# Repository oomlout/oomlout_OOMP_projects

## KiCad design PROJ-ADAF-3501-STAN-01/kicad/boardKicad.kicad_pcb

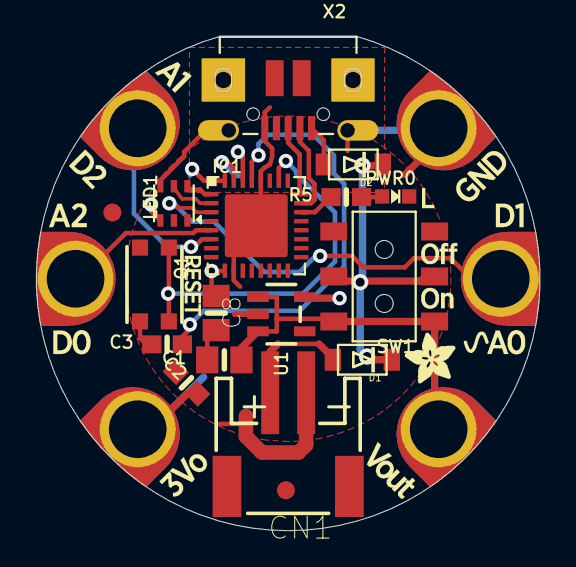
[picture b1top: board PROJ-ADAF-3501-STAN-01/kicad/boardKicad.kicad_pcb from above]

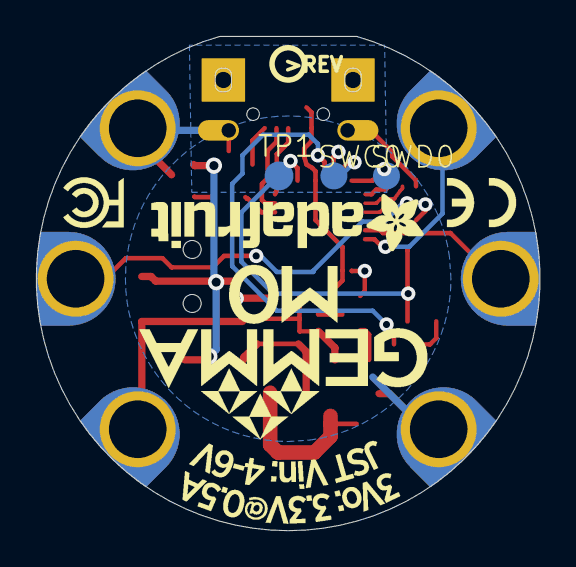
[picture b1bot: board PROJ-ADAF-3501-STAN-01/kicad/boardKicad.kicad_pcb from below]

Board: 16 copper layers, 28.0 x 27.5 mm, 29 parts (5 on the bottom side), 19 nets.

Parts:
B0, B1, B2: SEWTAP-ALLIGATOR; SEWALLI
C1, C8: 10uF; 0805-NO
C2, C3: 1uF; 0603-NO
CN1: JST-PH; JSTPH2
D1, D2: SCHOTTKY; SOD-123FL
GND0: SEWTAP-ALLIGATOR; SEWALLI
IC1: ATSAMD21E; QFN32_5MM
LED1: AP102-2020; APA102_2020
PWR0: red; CHIPLED_0603_NOOUTLINE
Q1: reset; BTN_KMR2_4.6X2.8
R5: 1K; 0603-NO
SW1: EG1218; EG1390
SWC0: TPTP15R; TP15R
SWD0: TPTP15R; TP15R
TP1: TPTP16R; TP16R
U1: AP2112K-3.3; SOT23-5
U$1, U$6: FIDUCIAL_1MM
U$7: GEMMA_M0_BOTTOM
U$8: GEMMA_M0_TOP
U$10: PCBFEAT-REV-040
UNK3V3: SEWTAP-ALLIGATOR; SEWALLI
VBAT0: SEWTAP-ALLIGATOR; SEWALLI
X2: MicroUSB; 4UCONN_20329_V2

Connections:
3.3V: C2.1, C8.1, IC1.9, IC1.30, LED1.3, U1.5, UNK3V3.P$1
D0_SDA_TX: B0.P$1, IC1.5
D1_A0: B1.P$1, IC1.3
D2_SCL_RX: B2.P$1, IC1.6
D3: IC1.1, LED1.6
D4: IC1.2, LED1.5
D13: IC1.22, R5.2
D+: IC1.24, X2.D+
D-: IC1.23, X2.D-
GND: C1.2, C2.2, C3.2, C8.2, CN1.1, GND0.P$1, IC1.10, IC1.28, IC1.33, LED1.4, PWR0.C, Q1.B, Q1.B', U1.2, X2.BASE@1, X2.BASE@2, X2.GND, X2.SPRT@1, X2.SPRT@2, X2.SPRT@3, X2.SPRT@4
unnamed: PWR0.A, R5.1
SWCLK: IC1.31, SWC0.TP
SWDIO: IC1.32, SWD0.TP
VBAT: CN1.2, D1.A
VBUS: D2.A, X2.VBUS
VDDCORE: C3.1, IC1.29
VHIGH: D1.C, D2.C, SW1.P1, SW1.P2
VOUT: C1.1, SW1.O1, SW1.O2, U1.1, U1.3, VBAT0.P$1
~RESET: IC1.26, Q1.A, Q1.A', TP1.TP

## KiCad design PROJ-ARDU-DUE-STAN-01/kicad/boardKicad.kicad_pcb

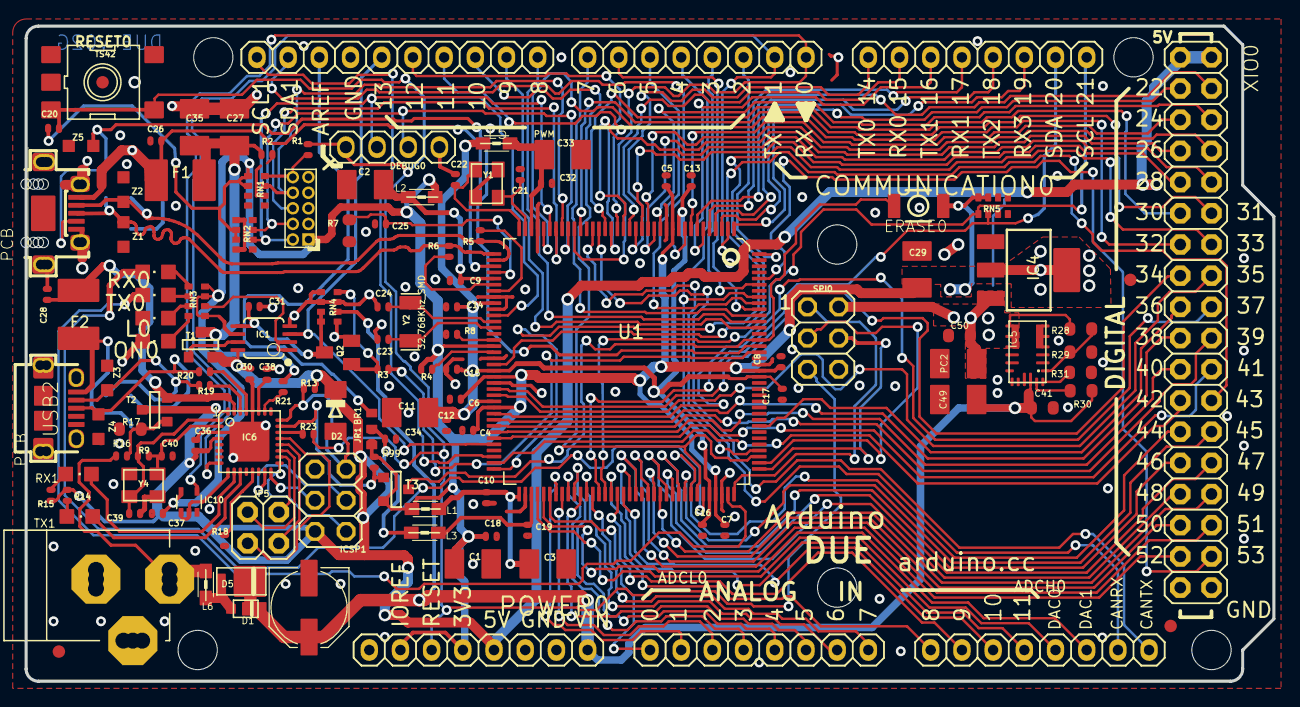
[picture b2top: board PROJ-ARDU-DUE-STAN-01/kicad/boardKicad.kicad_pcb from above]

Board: 2 copper layers, 101.6 x 53.3 mm, 147 parts (0 on the bottom side), 150 nets.

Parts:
@HOLE0, @HOLE1, @HOLE2, @HOLE3, @HOLE4, @HOLE5: (no value)
ADCH0: FH254-108DF08500V; 1X08
ADCL0: FH254-108DF08500V; 1X08
BR1: NM; J0402
C1, C2, C3, C11, C27, C29, C33, C35, C49: 22uF; SMC_B
C4, C5, C6, C7, C8, C9, C10, C12, C13, C14, C15, C16, C17, C18, C19, C28, C30, C31, C32, C34, C36, C37: 100nF; C0402
C20, C26: 10n; C0402
C21, C22, C23, C24, C25, C39, C40: 22pF; C0402
C38: 1uF; C0402
C41, C50: 100nF; C0603-ROUND
CN2: PINHEAD-2x5-P1.27; PINHEAD_2X05_127
COMMUNICATION0: FH254-108DF08500V; 1X08
D1: MSS1P3L-M3/89A; MICROSMP
D2: CD1206-S01575; MINIMELF
D5: SS1P3L; DO220AAL
DEBUG0: PH1X4-THT
ERASE0: 157SW; SMD_157SW
F1, F2: MF-MSMF050-2 500mA; L1812
FID1, FID2, FID3, FID4: FIDUCIALMOUNT; FIDUCIA-MOUNT
IC1: LMV358IDGKR; MSOP08
IC4: NX1117CE33Z; SOT223
IC5: MPM3610; QFN-20
IC6: ATMEGA16U2-MU; MLF32
IC10: 74LVC1G125DCKR; SC70-5
ICSP1: ICSP; 2X03
JP5: 2x2M - NM; 2X02
JR1: 0R; R0402
L0: Yellow; CHIPLED_0805
L1, L2, L3, L5, L6: MH2029-300Y; 0805
ON0: Green; CHIPLED_0805
PC1: 47uF; PANASONIC_D
PC2: 22uF; SMC_B
POWER0: FH254-108DF08500V; 1X08
PWMH0: FH254-110DF08500V; 1X10
PWML0: FH254-108DF08500V; 1X08
Q2: BC847B; SOT23
R1: 0R; R0402
R2, R13, R18, R99: 10K; R0402
R3, R14, R15, R21, R23: 1K; R0402
R4, R16: 100k; R0402
R5, R6: 39R 1%; R0402
R7: 6K8; R0603-ROUND
R8: 0R-DNP; R0402
R9: 1M; R0402
R17: 75K; R0603-ROUND
R19, R20: 22R; R0402
R28: 100K_1%; R0603-ROUND
R29: 19K1_0,1%; R0603-ROUND
R30: 100k; R0603-ROUND
R31: 56k; R0603-ROUND
RESET0: TS42
RN1, RN2, RN4: 100k; CAY16
RN3: 1K; CAY16
RN5: 1K5; CAY16
RX0, RX1: Yellow; CHIPLED_0805
SPI0: ICSP; 2X03
T1, T2, T3: PMV48XP; SOT-23
TX0, TX1: Yellow; CHIPLED_0805
U1: ATSAM3X8EA-AU; LQFP144
U$1, U$2: DNP; FRAME
UD+1, UD+2: DNP; TP-1.00MM
UD-1, UD-2: DNP; TP-1.00MM
UGND1, UGND2: DNP; TP-1.00MM
USB1: MCR-AB1-S-RA-SMT-TR; MCR-AB1-S-RA-SMT
USB2: MCR-B-S-RA-SMT-CS1TR; CON2_USB_MICRO_B_AT
UVB1, UVB2: DNP; TP-1.00MM
X2: POWER-SUPPLY; POWERSUPPLY_DC-21MM
XIO0: 18x2F-H8.5; 2X18
Y1: 12mHz-12pF-K7; CRYSTAL-3.2-2.5
Y2: 32,768Khz_SMD; RESONATOR_EPSON_FC_145
Y4: 16Mhz-KX-7; CRYSTAL-3.2-2.5
Z1, Z2, Z3, Z4, Z5: BRNCG0603MLC-05E; CT_CN0603

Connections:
8PB4: IC6.18, JP5.1
8PB5: IC6.19, JP5.3
8PB6: IC6.20, JP5.2
8PB7: IC6.21, JP5.4
16U2-TX: IC6.9, IC10.1, IC10.2
+3V3: BR1.3, C1.+, C4.2, C5.2, C6.2, C7.2, C8.2, C18.2, C20.2, C29.+, C37.1, CN2.1, ERASE0.1, IC1.6, IC4.2, IC4.4, IC10.5, JR1.1, L1.1, L2.1, POWER0.2, POWER0.4, R4.2, R99.2, RN1.5, RN1.6, RN2.2, RN2.3, RN3.5, RN3.7, RN3.8, RN5.3, RN5.4, T3.2, U1.11, U1.52, U1.57, U1.62, U1.105, U1.125
+5V: C30.2, C36.1, C50.1, D2.C, IC1.8, IC4.3, IC5.7, IC5.8, IC5.9, IC5.20, IC6.4, IC6.32, ICSP1.2, PC2.+, POWER0.5, R13.2, R14.1, R15.1, R28.2, SPI0.2, T1.2, T2.1, XIO0.1, XIO0.2
AD0: ADCL0.1, U1.78
AD1: ADCL0.2, U1.79
AD2: ADCL0.3, U1.80
AD3: ADCL0.4, U1.81
AD4: ADCL0.5, U1.82
AD5: ADCL0.6, U1.83
AD6: ADCL0.7, U1.84
AD7: ADCL0.8, U1.85
AD8: ADCH0.1, U1.88
AD9: ADCH0.2, U1.89
AD10: ADCH0.3, U1.90
AD11(TXD3): ADCH0.4, U1.91
AD14(RXD3): U1.92, XIO0.33
AREF: BR1.1, PWMH0.8
AVREF: C19.2, L3.2, U1.75
AVREFL: BR1.2, C34.2, JR1.2, L3.1
BD+: R20.2, UD+2.X, USB2.P3, Z4.2
BD-: R19.2, UD-2.X, USB2.P2, Z3.2
CANRX0: ADCH0.7, U1.24
CANTX0: ADCH0.8, U1.23
CANTX1/IO: U1.140, XIO0.34
CMP: C31.2, IC1.5, Q2.3, RN4.3, RN4.4
D+: R6.1, U1.37, UD-1.X, USB1.3, Z1.1
D-: R5.1, U1.38, UD+1.X, USB1.2, Z2.1
DAC0(CANRX1): ADCH0.5, U1.76
DAC1: ADCH0.6, U1.77
DTR: IC6.13, R18.1
ERASE_CMD: IC6.23, R99.1, T3.3
ERASE_S: ERASE0.2, T3.1, U1.130
GATE_CMD: IC1.7, T1.3
GND: C1.-, C2.-, C3.-, C4.1, C5.1, C6.1, C7.1, C8.1, C9.1, C10.1, C11.-, C12.1, C13.1, C14.1, C15.1, C16.1, C17.1, C18.1, C19.1, C21.2, C22.2, C23.2, C24.2, C25.2, C26.2, C27.-, C28.2, C29.-, C30.1, C31.1, C32.1, C33.-, C34.1, C35.-, C36.2, C37.2, C38.2, C39.2, C40.2, C41.2, C49.-, C50.2, CN2.3, CN2.5, CN2.9, DEBUG0.1, IC1.4, IC4.1, IC5.3, IC5.12, IC5.13, IC5.14, IC6.3, IC6.28, IC6.33, IC10.3, ICSP1.6, L0.C, ON0.C, PC1.-, PC2.-, POWER0.6, POWER0.7, PWMH0.7, Q2.2, R2.1, R7.1, R8.1, R17.1, R18.2, R29.1, R31.1, RESET0.1, RESET0.2, RN1.1, RN1.2, RN1.7, RN1.8, RN2.1, RN2.4, RN2.5, RN2.8, RN4.1, RN4.2, RN4.5, RN4.7, SPI0.6, U1.12, U1.33, U1.44, U1.46, U1.54, U1.58, U1.74, U1.106, U1.126, UGND1.X, UGND2.X, USB1.5, USB1.P$1, USB1.P$2, USB1.P$3, USB1.P$4, USB1.P$5, USB1.P$6, USB1.P$7, USB1.P$8, USB1.P$9, USB1.P$10, USB1.P$11, USB1.S1, USB1.S2, USB1.S3, USB1.S4, USB2.P5, USB2.P$1, USB2.P$2, USB2.P$3, USB2.P$4, USB2.P$5, USB2.P$6, USB2.P$7, USB2.P$8, USB2.S1, USB2.S2, USB2.S3, USB2.S4, USB2.S5, USB2.S6, X2.1, X2.3, XIO0.35, XIO0.36, Y1.2, Y1.4, Y4.2, Y4.4, Z1.2, Z2.2, Z3.1, Z4.1, Z5.1
JTAG_RESET: CN2.10, R1.1, RN1.4
JTAG_TCK: CN2.4, DEBUG0.2, RN2.7, U1.28
JTAG_TDI: CN2.8, RN1.3, U1.29
JTAG_TDO: CN2.6, U1.30
JTAG_TMS: CN2.2, DEBUG0.3, RN2.6, U1.31
L13: IC1.1, IC1.2, RN3.6
MASTER-RESET: C20.1, DEBUG0.4, POWER0.3, R1.2, R23.2, RESET0.3, RESET0.4, SPI0.5, U1.47
MISO: SPI0.1, U1.108
MISO2: IC6.17, ICSP1.1
MOSI: SPI0.4, U1.109
MOSI2: IC6.16, ICSP1.4
unnamed: IC6.26, R21.1
unnamed: L0.A, RN3.3
unnamed: ON0.A, RN3.4
unnamed: R15.2, RX1.A
unnamed: R8.2, U1.51
unnamed: Q2.1, R3.2, RN4.8
unnamed: R4.1, U1.53
unnamed: D1.A, D5.P$2, L6.1
unnamed: R5.2, U1.43
unnamed: R6.2, U1.42
unnamed: R14.2, TX1.A
unnamed: R16.1, R17.2, T2.3
unnamed: IC5.1, R28.1, R29.2
unnamed: IC5.17, R30.2
unnamed: IC5.18, R31.2
unnamed: RN3.1, RX0.A
unnamed: RN3.2, TX0.A
PIN22: U1.1, XIO0.3
PIN23: U1.7, XIO0.4
PIN24: U1.8, XIO0.5
PIN25: U1.13, XIO0.6
PIN26: U1.14, XIO0.7
PIN27: U1.15, XIO0.8
PIN28: U1.16, XIO0.9
PIN29: U1.19, XIO0.10
PIN30: U1.22, XIO0.11
PIN31: U1.26, XIO0.12
PIN32: U1.32, XIO0.13
PIN33: U1.55, XIO0.14
PIN34: U1.59, XIO0.15
PIN35: U1.60, XIO0.16
PIN36: U1.116, XIO0.17
PIN37: U1.63, XIO0.18
PIN38: U1.64, XIO0.19
PIN39: U1.65, XIO0.20
PIN40: U1.66, XIO0.21
PIN41: U1.67, XIO0.22
PIN42: U1.71, XIO0.23
PIN43: U1.72, XIO0.24
PIN44: U1.101, XIO0.25
PIN45: U1.100, XIO0.26
PIN46: U1.99, XIO0.27
PIN47: U1.98, XIO0.28
PIN48: U1.97, XIO0.29
PIN49: U1.96, XIO0.30
PIN50: U1.95, XIO0.31
PIN51: U1.94, XIO0.32
PWM2: PWML0.3, U1.144
PWM3: PWML0.4, U1.139
PWM5: PWML0.6, U1.136
PWM6: PWML0.7, U1.135
PWM7: PWML0.8, U1.134
PWM8: PWMH0.1, U1.133
PWM9: PWMH0.2, U1.132
PWM11: PWMH0.4, U1.20
PWM12: PWMH0.5, U1.21
PWM13: IC1.3, PWMH0.6, U1.68
RD+: IC6.29, R20.1
RD-: IC6.30, R19.1
RESET2: D2.A, IC6.24, ICSP1.5, R13.1
RESET_CMD: IC6.22, R23.1
RXD0: IC10.4, PWML0.1, U1.27
RXD1: COMMUNICATION0.6, U1.3
RXD2: COMMUNICATION0.4, U1.5
RXD3: COMMUNICATION0.2, U1.18
RXL: RX0.C, U1.103
RXL-U2: IC6.10, RX1.C
SCK2: IC6.15, ICSP1.3
SCL0-3: COMMUNICATION0.8, RN5.5, U1.87
SCL1: PWMH0.10, U1.70
SDA0-3: COMMUNICATION0.7, RN5.6, U1.86
SDA1: PWMH0.9, U1.9
SPCK: SPI0.3, U1.110
SS0/PWM10: PWMH0.3, U1.102, U1.111
SS1/PWM4: PWML0.5, U1.112, U1.137
TXD0: IC6.8, PWML0.2, U1.2
TXD1: COMMUNICATION0.5, U1.4
TXD2: COMMUNICATION0.3, U1.6
TXD3: COMMUNICATION0.1, U1.17
TXL: TX0.C, U1.107
TXL-U2: IC6.11, TX1.C
UOTGID: U1.129, USB1.4, Z5.2
UOTGVBOF: R3.1, U1.128
USBVCC: C27.+, C35.+, F1.1, R2.2, R21.2, T1.1
USBVCCU2: C28.1, F2.1, IC6.31, T2.2
VBG: C25.1, R7.2, U1.40
VDDANA: C3.+, C10.2, L1.2, U1.73
VDDOUT: C11.+, C12.2, C13.2, C14.2, C15.2, C16.2, C17.2, L5.1, U1.10, U1.45, U1.56, U1.61, U1.104, U1.124
VDDOUTMI: C2.+, C9.2, L2.2, U1.41
VDDPLL: C32.2, C33.+, L5.2, U1.34
VIN: C41.1, C49.+, D1.K, D5.P$1, IC5.16, PC1.+, POWER0.8, R30.1, RN4.6
VIN+: L6.2, R16.2, X2.2
VUCAP: C38.1, IC6.27
XIN: C22.1, U1.36, Y1.1
XIN32: C24.1, U1.48, Y2.P$2
XOUT: C21.1, U1.35, Y1.3
XOUT32: C23.1, U1.49, Y2.P$1
XT1: C39.1, IC6.1, R9.1, Y4.1
XT2: C40.1, IC6.2, R9.2, Y4.3
XUSB: C26.1, F1.2, U1.39, USB1.1, UVB1.X
XVCC: F2.2, USB2.P1, UVB2.X

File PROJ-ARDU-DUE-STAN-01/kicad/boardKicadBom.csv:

"Id";"Designator";"Package";"Quantity";"Designation";"Supplier and ref";
1;"C3,C29,PC2,C1,C35,C49,C2,C11,C33,C27";"SMC_B";10;"22uF";;;
2;"C39,C23,C24,C25,C40,C21,C22";"C0402";7;"22pF";;;
3;"R21,R23,R15,R3,R14";"R0402";5;"1K";;;
4;"USB1";"MCR-AB1-S-RA-SMT";1;"MCR-AB1-S-RA-SMT-TR";;;
5;"R29";"R0603-ROUND";1;"19K1_0,1%";;;
6;"Z3,Z1,Z4,Z5,Z2";"CT_CN0603";5;"BRNCG0603MLC-05E";;;
7;"C16,C15,C34,C12,C17,C32,C19,C6,C30,C14,C8,C13,C4,C36,C28,C9,C37,C5,C31,C7,C18,C10";"C0402";22;"100nF";;;
8;"L5,L3,L1,L2,L6";"0805";5;"MH2029-300Y";;;
9;"R28";"R0603-ROUND";1;"100K_1%";;;
10;"T1,T2,T3";"SOT-23";3;"PMV48XP";;;
11;"C41,C50";"C0603-ROUND";2;"100nF";;;
12;"ICSP1,SPI0";"2X03";2;"ICSP";;;
13;"RX1,TX0,L0,TX1,RX0";"CHIPLED_0805";5;"Yellow";;;
14;"UD-1,UVB2,UGND2,UD+1,UD-2,UVB1,UGND1,UD+2";"TP-1.00MM";8;"DNP";;;
15;"R19,R20";"R0402";2;"22R";;;
16;"R1,JR1";"R0402";2;"0R";;;
17;"R99,R13,R18,R2";"R0402";4;"10K";;;
18;"RN2,RN1,RN4";"CAY16";3;"100k";;;
19;"FID3,FID1,FID4,FID2";"FIDUCIA-MOUNT";4;"FIDUCIALMOUNT";;;
20;"IC4";"SOT223";1;"NX1117CE33Z";;;
21;"R7";"R0603-ROUND";1;"6K8";;;
22;"USB2";"CON2_USB_MICRO_B_AT";1;"MCR-B-S-RA-SMT-CS1TR";;;
23;"IC5";"QFN-20";1;"MPM3610";;;
24;"BR1";"J0402";1;"NM";;;
25;"ADCL0,PWML0,COMMUNICATION0,ADCH0,POWER0";"1X08";5;"FH254-108DF08500V";;;
26;"PWMH0";"1X10";1;"FH254-110DF08500V";;;
27;"RN5";"CAY16";1;"1K5";;;
28;"R5,R6";"R0402";2;"39R 1%";;;
29;"@HOLE3,@HOLE4,@HOLE0,@HOLE5,@HOLE1,@HOLE2";"";6;"";;;
30;"RN3";"CAY16";1;"1K";;;
31;"RESET0";"TS42";1;"TS42";;;
32;"R30";"R0603-ROUND";1;"100k";;;
33;"PC1";"PANASONIC_D";1;"47uF";;;
34;"D5";"DO220AAL";1;"SS1P3L";;;
35;"U$1,U$2";"FRAME";2;"DNP";;;
36;"R17";"R0603-ROUND";1;"75K";;;
37;"F1,F2";"L1812";2;"MF-MSMF050-2 500mA";;;
38;"IC10";"SC70-5";1;"74LVC1G125DCKR";;;
39;"DEBUG0";"PH1X4-THT";1;"";;;
40;"C26,C20";"C0402";2;"10n";;;
41;"Y2";"RESONATOR_EPSON_FC_145";1;"32,768Khz_SMD";;;
42;"D2";"MINIMELF";1;"CD1206-S01575";;;
43;"D1";"MICROSMP";1;"MSS1P3L-M3/89A";;;
44;"XIO0";"2X18";1;"18x2F-H8.5";;;
45;"R16,R4";"R0402";2;"100k";;;
46;"ERASE0";"SMD_157SW";1;"157SW";;;
47;"JP5";"2X02";1;"2x2M - NM";;;
48;"Q2";"SOT23";1;"BC847B";;;
49;"R31";"R0603-ROUND";1;"56k";;;
50;"U1";"LQFP144";1;"ATSAM3X8EA-AU";;;
51;"IC6";"MLF32";1;"ATMEGA16U2-MU";;;
52;"Y1";"CRYSTAL-3.2-2.5";1;"12mHz-12pF-K7";;;
53;"Y4";"CRYSTAL-3.2-2.5";1;"16Mhz-KX-7";;;
54;"X2";"POWERSUPPLY_DC-21MM";1;"POWER-SUPPLY";;;
55;"R9";"R0402";1;"1M";;;
56;"ON0";"CHIPLED_0805";1;"Green";;;
57;"IC1";"MSOP08";1;"LMV358IDGKR";;;
58;"R8";"R0402";1;"0R-DNP";;;
59;"C38";"C0402";1;"1uF";;;
60;"CN2";"PINHEAD_2X05_127";1;"PINHEAD-2x5-P1.27";;;

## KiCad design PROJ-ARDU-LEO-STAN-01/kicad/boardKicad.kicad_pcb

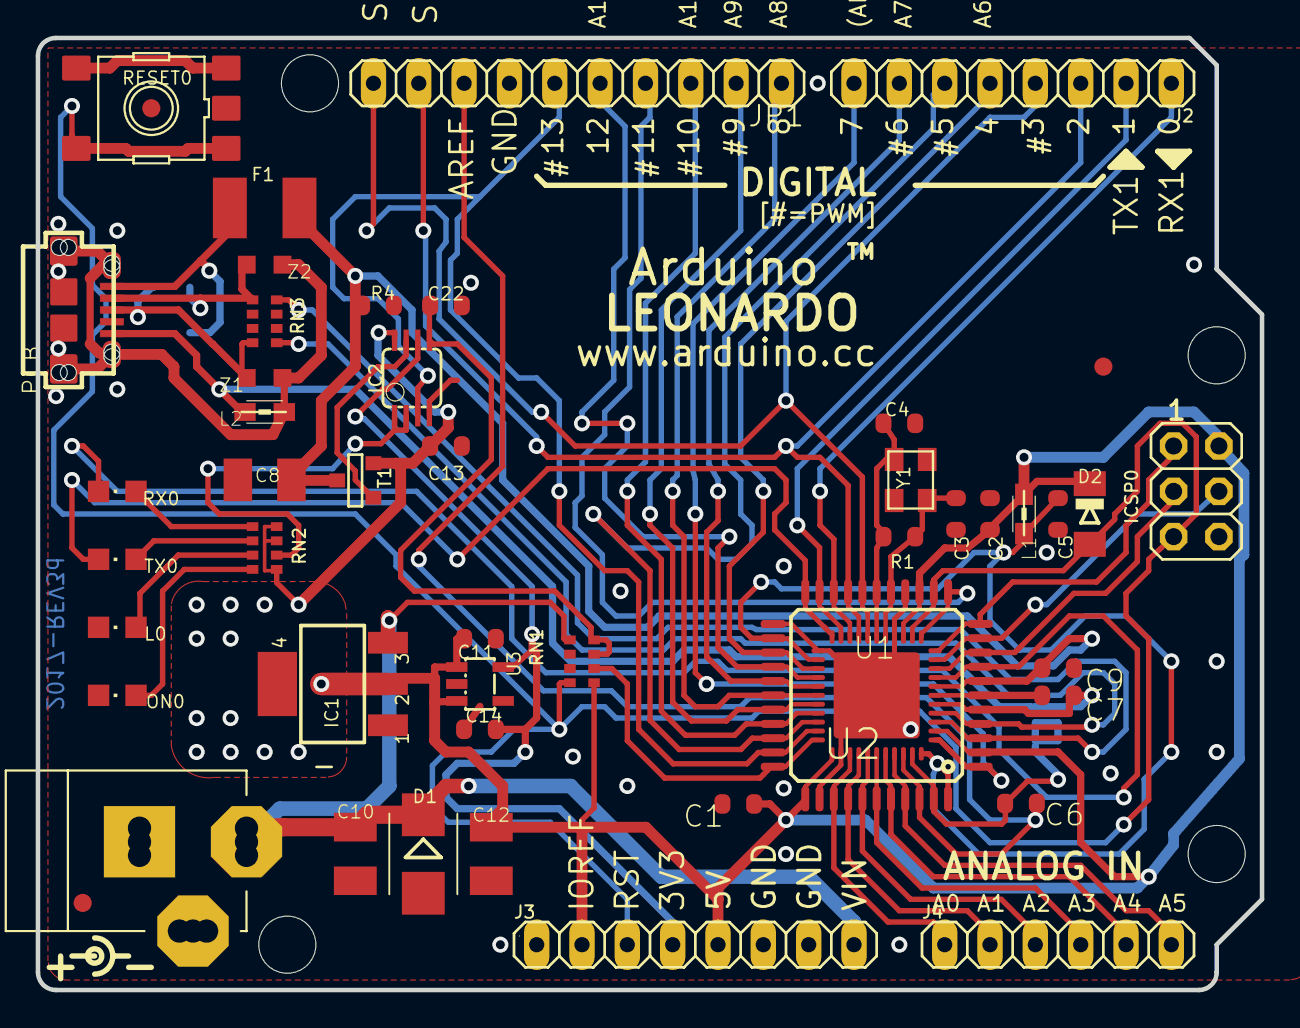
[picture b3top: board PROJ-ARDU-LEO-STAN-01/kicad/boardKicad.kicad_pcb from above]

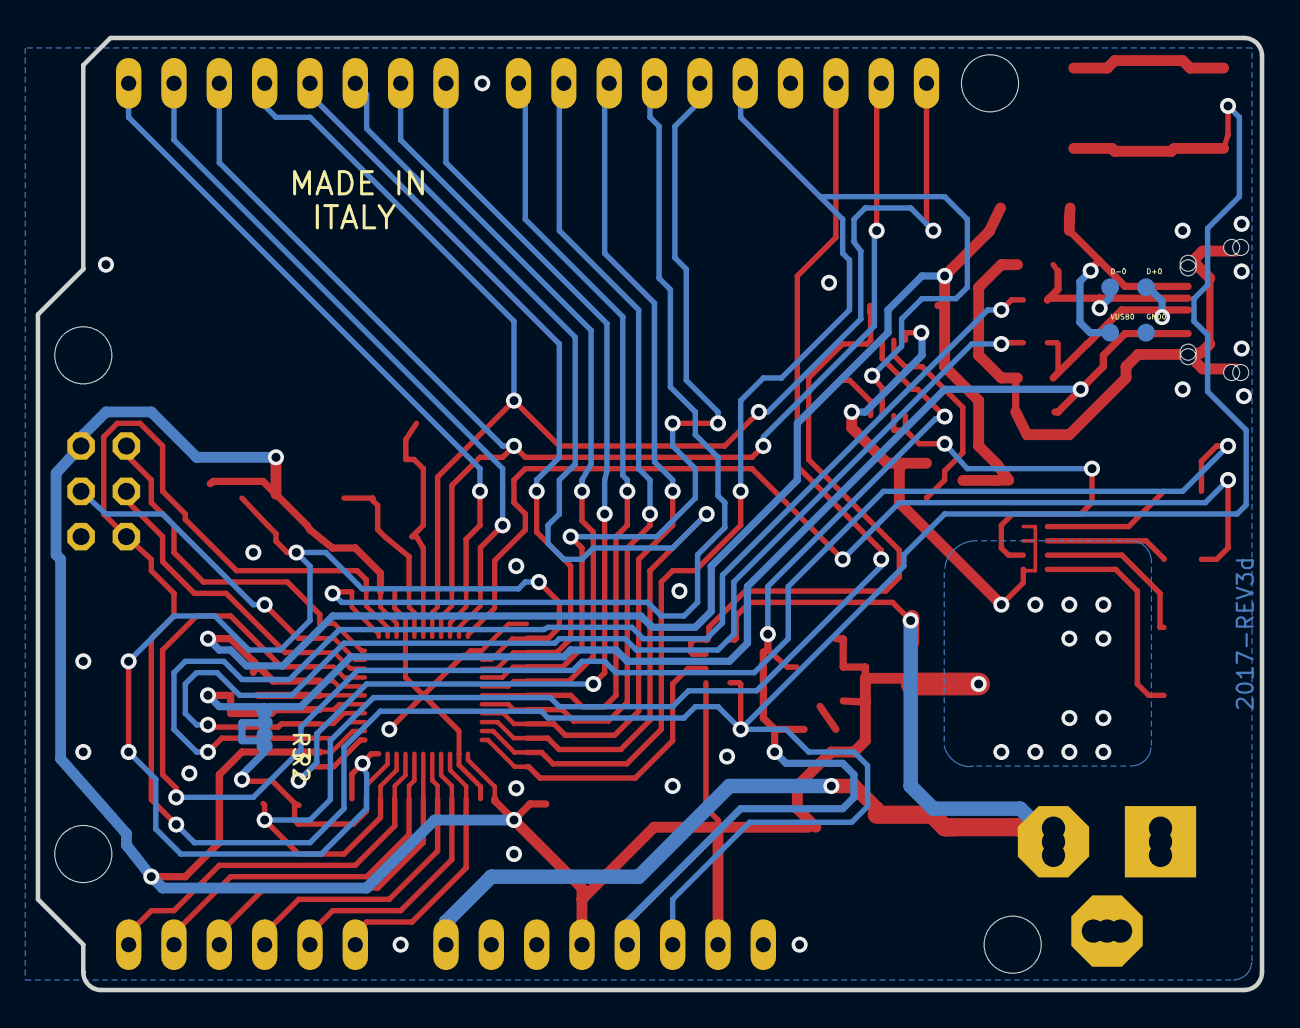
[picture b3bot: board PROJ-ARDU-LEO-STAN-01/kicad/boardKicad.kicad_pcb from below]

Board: 2 copper layers, 68.6 x 53.3 mm, 60 parts (2 on the bottom side), 51 nets.

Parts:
@HOLE0, @HOLE1, @HOLE2, @HOLE3: (no value)
C1, C2, C6, C9, C13, C22: 100n; C0603-ROUND
C3, C4: 22p; C0603-ROUND
C5, C7, C11, C14: 1uF; C0603-ROUND
C8, C10, C12: 10u; SMC_B
D1: M7; SMB
D2: CD1206-S01575; MINIMELF
D+0: DNP; TP-1.00MM
D-0: DNP; TP-1.00MM
EXTPOWER0: POWERSUPPLY_DC21MMX; POWERSUPPLY_DC-21MM
F1: MF-MSMF050-2 500mA; L1812
FID1, FID2, FID3: DNP; FD-1-1.5
FRAME1: DNP; FRAME
GND0: DNP; TP-1.00MM
IC1: NCP1117ST50T3G; SOT223
IC2: LMV358IDGKR; MSOP08
ICSP0: ICSP; 2X03
J1: USB Micro; CON2_USB_MICRO_B_AT
J2, J3: 8x1F-H8.5; 1X08
J4: 6x1F-H8.5; 1X06
JP1: 10x1F-H8.5; 1X10
L0: Yellow; CHIPLED_0805
L1, L2: MH2029-300Y; 0805
ON0: Green; CHIPLED_0805
R1: 1M; R0603-ROUND
R2, R3: NM; R0402
R4: 10K; R0603-ROUND
RESET0: TS42
RN1: 10K; CAY16
RN2: 1K; CAY16
RN3: 22R; CAY16
RX0: Yellow; CHIPLED_0805
T1: FDN340P; SOT-23
TX0: Yellow; CHIPLED_0805
U1: ATMEGA32U4-XUMU; QFN44ML7X7
U2: ATMEGA32U4-XUAU; TQFP44-PAD
U3: LP2985-33DBVR; SOT23-DBV
VUSB0: DNP; TP-1.00MM
Y1: 16MHz KX-7; CRYSTAL-3.2-2.5
Z1, Z2: CG0603MLC-05E; CT_CN0603

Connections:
+3V3: C14.2, IC2.6, J3.4, U3.5
+5V: C1.1, C2.1, C11.2, C12.+, C13.1, D2.C, IC1.2, IC1.4, IC2.8, ICSP0.2, J3.2, J3.5, L1.1, RN1.5, RN2.1, RN2.3, RN2.4, T1.2, U1.2, U1.14, U1.34, U2.2, U2.14, U2.34, U3.1, U3.3
A0: J4.1, U1.36, U2.36
A1: J4.2, U1.37, U2.37
A2: J4.3, U1.38, U2.38
A3: J4.4, U1.39, U2.39
A4: J4.5, U1.40, U2.40
A5: J4.6, U1.41, U2.41
AGND: C6.1, R2.1, U1.43, U2.43
AREF: C6.2, JP1.8, U1.42, U2.42
AVCC: C5.1, L1.2, U1.24, U1.44, U2.24, U2.44
CMP: C22.2, IC2.5, RN1.7, RN1.8
D0/RX: J2.1, U1.20, U2.20
D1/TX: J2.2, U1.21, U2.21
D2/SDA: J2.3, JP1.9, U1.19, U2.19
D3/SCL: J2.4, JP1.10, U1.18, U2.18
D4: J2.5, U1.25, U2.25
D5*: J2.6, U1.31, U2.31
D6*: J2.7, U1.27, U2.27
D7: J2.8, U1.1, U2.1
D+: D+0.X, J1.P3, RN3.8, Z1.1
D-: D-0.X, J1.P2, RN3.5, Z2.1
GATE_CMD: IC2.7, T1.3
GND: C1.2, C2.2, C3.1, C4.2, C5.2, C8.-, C9.1, C10.-, C11.1, C12.-, C13.2, C14.1, C22.1, D1.A, EXTPOWER0.1, EXTPOWER0.3, GND0.X, IC1.1, IC2.4, ICSP0.6, J1.S1, J1.S2, J1.S3, J1.S4, J1.S5, J1.S6, J3.6, J3.7, JP1.7, L0.C, L2.2, ON0.C, R2.2, R3.1, R4.1, RESET0.3, RESET0.4, RN1.2, RN1.3, U1.15, U1.23, U1.35, U1.EXP, U2.15, U2.23, U2.35, U2.P$1, U3.2, Y1.2, Y1.4, Z1.2, Z2.2
HWB: RN1.6, U1.33, U2.33
IO8: JP1.1, U1.28, U2.28
IO9*: JP1.2, U1.29, U2.29
IO10*: JP1.3, U1.30, U2.30
IO11*: JP1.4, U1.12, U2.12
IO12: JP1.5, U1.26, U2.26
IO13*: IC2.3, JP1.6, U1.32, U2.32
LL: IC2.1, IC2.2, RN2.2
MISO: ICSP0.1, U1.11, U2.11
MOSI: ICSP0.4, U1.10, U2.10
unnamed: L0.A, RN2.7
unnamed: ON0.A, RN2.8
unnamed: RN2.6, TX0.A
unnamed: RN2.5, RX0.A
RD+: RN3.1, U1.4, U2.4
RD-: RN3.4, U1.3, U2.3
RESET: D2.A, ICSP0.5, J3.3, RESET0.1, RESET0.2, RN1.4, U1.13, U2.13
RXLED: RX0.C, U1.8, U2.8
SCK: ICSP0.3, U1.9, U2.9
TXLED: TX0.C, U1.22, U2.22
UCAP: C7.1, U1.6, U2.6
UGND: C7.2, J1.P5, L2.1, R3.2, U1.5, U2.5
VIN: C10.+, D1.C, EXTPOWER0.2, IC1.3, J3.8, RN1.1
VUSB: C8.+, C9.2, F1.1, R4.2, T1.1, U1.7, U2.7
XTAL1: C4.1, R1.1, U1.17, U2.17, Y1.1
XTAL2: C3.2, R1.2, U1.16, U2.16, Y1.3
XUSB: F1.2, J1.P1, VUSB0.X

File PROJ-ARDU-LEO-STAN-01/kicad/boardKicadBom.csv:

"Id";"Designator";"Package";"Quantity";"Designation";"Supplier and ref";
1;"C4,C3";"C0603-ROUND";2;"22p";;;
2;"FID3,FID1,FID2";"FD-1-1.5";3;"DNP";;;
3;"D+0,VUSB0,D-0,GND0";"TP-1.00MM";4;"DNP";;;
4;"C5,C11,C14,C7";"C0603-ROUND";4;"1uF";;;
5;"IC1";"SOT223";1;"NCP1117ST50T3G";;;
6;"TX0,L0,RX0";"CHIPLED_0805";3;"Yellow";;;
7;"@HOLE0,@HOLE1,@HOLE2,@HOLE3";"";4;"";;;
8;"IC2";"MSOP08";1;"LMV358IDGKR";;;
9;"C13,C22,C2,C9,C6,C1";"C0603-ROUND";6;"100n";;;
10;"J4";"1X06";1;"6x1F-H8.5";;;
11;"Z1,Z2";"CT_CN0603";2;"CG0603MLC-05E";;;
12;"D1";"SMB";1;"M7";;;
13;"J1";"CON2_USB_MICRO_B_AT";1;"USB Micro";;;
14;"EXTPOWER0";"POWERSUPPLY_DC-21MM";1;"POWERSUPPLY_DC21MMX";;;
15;"L2,L1";"0805";2;"MH2029-300Y";;;
16;"RN3";"CAY16";1;"22R";;;
17;"ICSP0";"2X03";1;"ICSP";;;
18;"JP1";"1X10";1;"10x1F-H8.5";;;
19;"RN1";"CAY16";1;"10K";;;
20;"Y1";"CRYSTAL-3.2-2.5";1;"16MHz KX-7";;;
21;"RESET0";"TS42";1;"TS42";;;
22;"J2,J3";"1X08";2;"8x1F-H8.5";;;
23;"ON0";"CHIPLED_0805";1;"Green";;;
24;"D2";"MINIMELF";1;"CD1206-S01575";;;
25;"F1";"L1812";1;"MF-MSMF050-2 500mA";;;
26;"C8,C12,C10";"SMC_B";3;"10u";;;
27;"R1";"R0603-ROUND";1;"1M";;;
28;"T1";"SOT-23";1;"FDN340P";;;
29;"U2";"TQFP44-PAD";1;"ATMEGA32U4-XUAU";;;
30;"R4";"R0603-ROUND";1;"10K";;;
31;"FRAME1";"FRAME";1;"DNP";;;
32;"U1";"QFN44ML7X7";1;"ATMEGA32U4-XUMU";;;
33;"RN2";"CAY16";1;"1K";;;
34;"U3";"SOT23-DBV";1;"LP2985-33DBVR";;;
35;"R2,R3";"R0402";2;"NM";;;

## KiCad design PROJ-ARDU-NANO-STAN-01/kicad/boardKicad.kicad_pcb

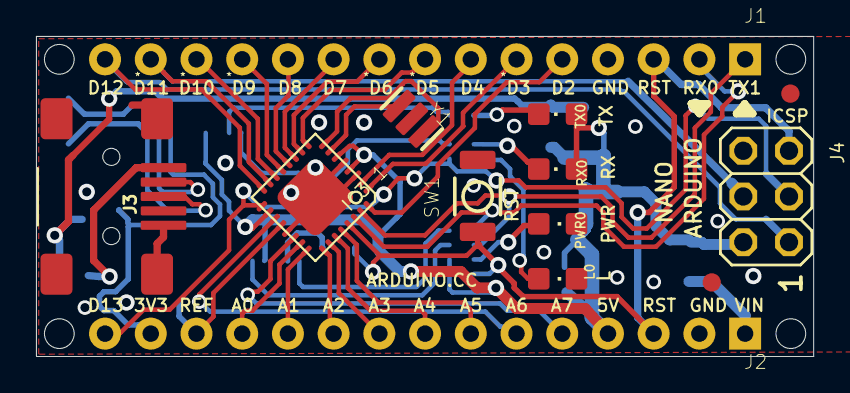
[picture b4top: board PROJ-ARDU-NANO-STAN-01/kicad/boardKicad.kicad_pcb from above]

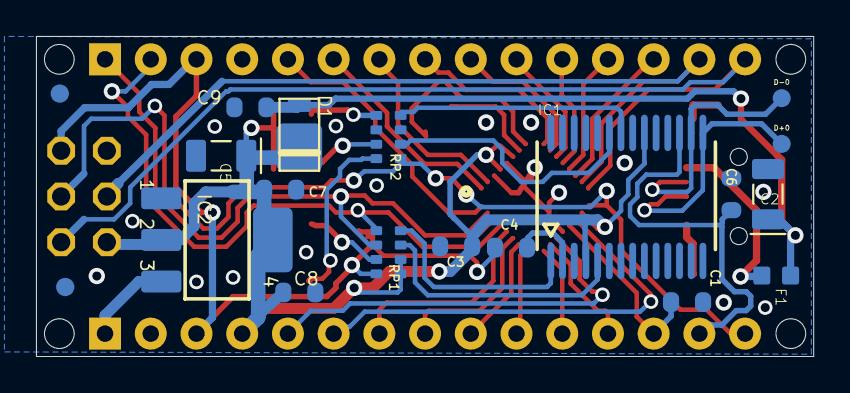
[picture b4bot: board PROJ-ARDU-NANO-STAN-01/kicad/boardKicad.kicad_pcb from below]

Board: 2 copper layers, 43.2 x 17.8 mm, 37 parts (17 on the bottom side), 43 nets.

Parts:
@HOLE0, @HOLE1, @HOLE2, @HOLE3: (no value)
C1, C4, C6, C9: 100nF; C0603-ROUND
C2, C5: 4,7uF_16V; TAN-A
C3, C7, C8: 1uF; C0603-ROUND
D1: SS1P3L; DO220AAL
D+0: DNP; TP-1.00MM
D-0: DNP; TP-1.00MM
F1: MFFSMF050; 0603-1608X90N
FRAME1: DNP; FRAME
IC1: FT232RL; SSOP28
IC2: LM1117IMPX-5.0; LINEAR_SOT223
IC3: 328P-MUR; VQFN32
J1, J2: XXXX_STRIPNANO; HEAD15-NOSS
J3: USB-MINI-B_2
J4: 2X03
L0: Yellow; CHIPLED_0805
PWR0: Green; CHIPLED_0805
RP1, RP2: 1K; CAY16
RX0: Red; CHIPLED_0805
SW1: RESET; SMD_157SW
TX0: Green; CHIPLED_0805
U$4, U$5, U$53, U$54: DNP; FD-1-1.5
Y1: 16MHz; RESONATOR

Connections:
3V3: C6.2, IC1.17, J2.14
+5V: C3.1, C5.1, C7.1, C8.1, D1.P$1, IC1.4, IC1.20, IC2.2, IC2.4, IC3.4, IC3.6, IC3.18, J2.4, J4.2, RP1.5, RP1.6, RX0.A, TX0.A
A0: IC3.23, J2.12
A1: IC3.24, J2.11
A2: IC3.25, J2.10
A3: IC3.26, J2.9
A4: IC3.27, J2.8
A5: IC3.28, J2.7
A6: IC3.19, J2.6
A7: IC3.22, J2.5
AREF: C1.1, IC3.20, J2.13
COM: C1.2, C2.2, C3.2, C5.2, C6.1, C7.2, C8.2, C9.2, IC1.7, IC1.18, IC1.21, IC1.25, IC1.26, IC2.1, IC3.3, IC3.5, IC3.21, IC3.33, J1.4, J2.2, J3.1, J3.6, J3.7, J3.8, J3.9, J4.6, L0.C, PWR0.C, RP2.3, RP2.6, SW1.1, Y1.2
D0/RX: IC3.30, J1.2, RP1.1
D1/TX: IC3.31, J1.1, RP1.2
D2: IC3.32, J1.5
D3: IC3.1, J1.6
D4: IC3.2, J1.7
D5: IC3.9, J1.8
D6: IC3.10, J1.9
D7: IC3.11, J1.10
D8: IC3.12, J1.11
D9: IC3.13, J1.12
D10: IC3.14, J1.13
D11/MOSI: IC3.15, J1.14, J4.4
D12/MISO: IC3.16, J1.15, J4.1
D13/SCK: IC3.17, J2.15, J4.3, RP2.1
unnamed: IC3.8, Y1.3
unnamed: IC3.7, Y1.1
unnamed: PWR0.A, RP1.3
unnamed: C4.2, IC1.2
unnamed: D+0.X, IC1.15, J3.3
unnamed: D-0.X, IC1.16, J3.4
unnamed: L0.A, RP2.8
unnamed: IC1.23, RP2.2
unnamed: IC1.22, RP2.4
unnamed: RP2.5, TX0.C
unnamed: F1.2, J3.5
unnamed: RP2.7, RX0.C
RESET: C4.1, IC3.29, J1.3, J2.3, J4.5, RP1.4, SW1.2
RX: IC1.1, RP1.8
TX: IC1.5, RP1.7
VIN: IC2.3, J2.1
VUSB: C2.1, C9.1, D1.P$2, F1.1

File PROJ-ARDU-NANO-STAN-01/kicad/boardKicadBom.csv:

"Id";"Designator";"Package";"Quantity";"Designation";"Supplier and ref";
1;"TX0,PWR0";"CHIPLED_0805";2;"Green";;;
2;"@HOLE2,@HOLE0,@HOLE1,@HOLE3";"";4;"";;;
3;"J4";"2X03";1;"";;;
4;"D-0,D+0";"TP-1.00MM";2;"DNP";;;
5;"RX0";"CHIPLED_0805";1;"Red";;;
6;"U$5,U$4,U$54,U$53";"FD-1-1.5";4;"DNP";;;
7;"J3";"USB-MINI-B_2";1;"";;;
8;"Y1";"RESONATOR";1;"16MHz";;;
9;"J2,J1";"HEAD15-NOSS";2;"XXXX_STRIPNANO";;;
10;"FRAME1";"FRAME";1;"DNP";;;
11;"L0";"CHIPLED_0805";1;"Yellow";;;
12;"SW1";"SMD_157SW";1;"RESET";;;
13;"IC3";"VQFN32";1;"328P-MUR";;;
14;"C7,C3,C8";"C0603-ROUND";3;"1uF";;;
15;"C2,C5";"TAN-A";2;"4,7uF_16V";;;
16;"IC1";"SSOP28";1;"FT232RL";;;
17;"C1,C6,C9,C4";"C0603-ROUND";4;"100nF";;;
18;"D1";"DO220AAL";1;"SS1P3L";;;
19;"RP2,RP1";"CAY16";2;"1K";;;
20;"F1";"0603-1608X90N";1;"MFFSMF050";;;
21;"IC2";"LINEAR_SOT223";1;"LM1117IMPX-5.0";;;
